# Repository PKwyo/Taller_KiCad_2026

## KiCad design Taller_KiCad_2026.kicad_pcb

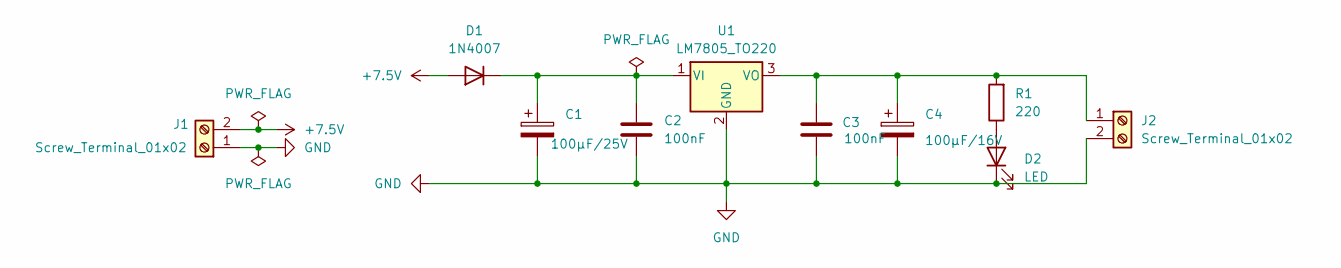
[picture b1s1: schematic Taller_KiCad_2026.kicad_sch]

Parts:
C1: 100µF/25V; CP_Radial_D5.0mm_P2.00mm
C2, C3: 100nF; C_Disc_D5.0mm_W2.5mm_P2.50mm
C4: 100µF/16V; CP_Radial_D5.0mm_P2.00mm
D1: 1N4007; D_DO-41_SOD81_P10.16mm_Horizontal
D2: LED; LED_D5.0mm
J1, J2: Screw_Terminal_01x02; TerminalBlock_Phoenix_MKDS-1,5-2-5.08_1x02_P5.08mm_Horizont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
R1: 220; R_Axial_DIN0207_L6.3mm_D2.5mm_P10.16mm_Horizontal
U1: LM7805_TO220; TO-220-3_Vertical

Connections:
+7.5V: D1.2 (A), J1.2
GND: C1.2, C2.2, C3.2, C4.2, D2.1 (K), J1.1, J2.2, U1.2 (GND)
unnamed: C1.1, C2.1, D1.1 (K), U1.1 (VI)
unnamed: D2.2 (A), R1.1
unnamed: C3.1, C4.1, J2.1, R1.2, U1.3 (VO)

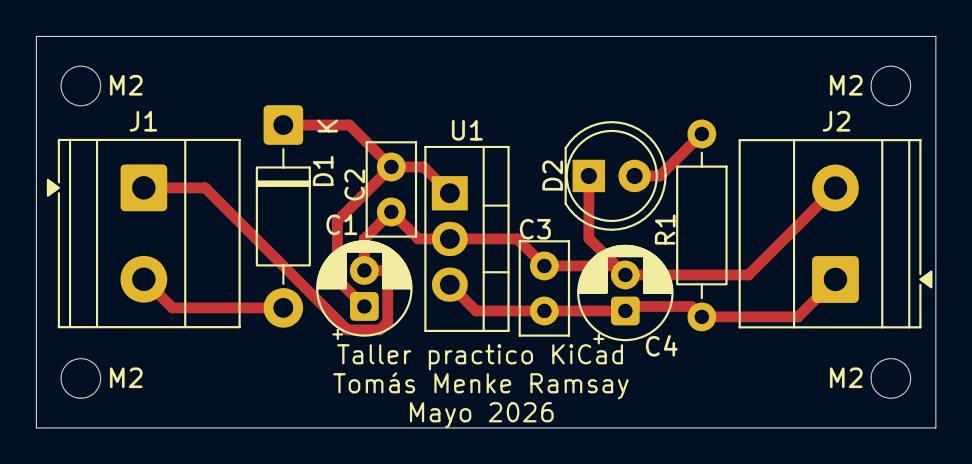
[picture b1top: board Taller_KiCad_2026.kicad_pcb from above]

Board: 2 copper layers, 50.0 x 21.8 mm, 14 parts (0 on the bottom side), 5 nets.

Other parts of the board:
M2, M2#2, M2#3, M2#4: MountingHole_2.2mm_M2

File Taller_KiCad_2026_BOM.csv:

"Referencia","cantidad","Valores","Componente","Exclude from BOM","Exclude from Board","Footprint","Datasheet"
"C1","1","100µF/25V","CAP","","","Capacitor_THT:CP_Radial_D5.0mm_P2.00mm",""
"C2,C3","2","100nF","CAP","","","Capacitor_THT:C_Disc_D5.0mm_W2.5mm_P2.50mm",""
"C4","1","100µF/16V","CAP","","","Capacitor_THT:CP_Radial_D5.0mm_P2.00mm",""
"D1","1","1N4007","DIODO","","","Diode_THT:D_DO-41_SOD81_P10.16mm_Horizontal","http://www.vishay.com/docs/88503/1n4001.pdf"
"D2","1","LED","LED","","","LED_THT:LED_D5.0mm",""
"J1,J2","2","Screw_Terminal_01x02","","","","TerminalBlock_Phoenix:TerminalBlock_Phoenix_MKDS-1,5-2-5.08_1x02_P5.08mm_Horizontal",""
"R1","1","220","RES","","","Resistor_THT:R_Axial_DIN0207_L6.3mm_D2.5mm_P10.16mm_Horizontal",""
"U1","1","LM7805_TO220","REGULADOR VOLTAJE","","","Package_TO_SOT_THT:TO-220-3_Vertical","https://www.onsemi.cn/PowerSolutions/document/MC7800-D.PDF"

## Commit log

2026-06-01 Rename poryecto.kicad_pcb to Taller_KiCad_2026.kicad_pcb
2026-06-01 Rename poryecto.kicad_pro to Taller_KiCad_2026.kicad_pro
2026-06-01 Rename poryecto.kicad_sch to Taller_KiCad_2026.kicad_sch
2026-06-01 Rename poryecto.csv to Taller_KiCad_2026_BOM.csv
2026-06-01 Rename poryecto.png to Taller_KiCad_2026_3D.png
